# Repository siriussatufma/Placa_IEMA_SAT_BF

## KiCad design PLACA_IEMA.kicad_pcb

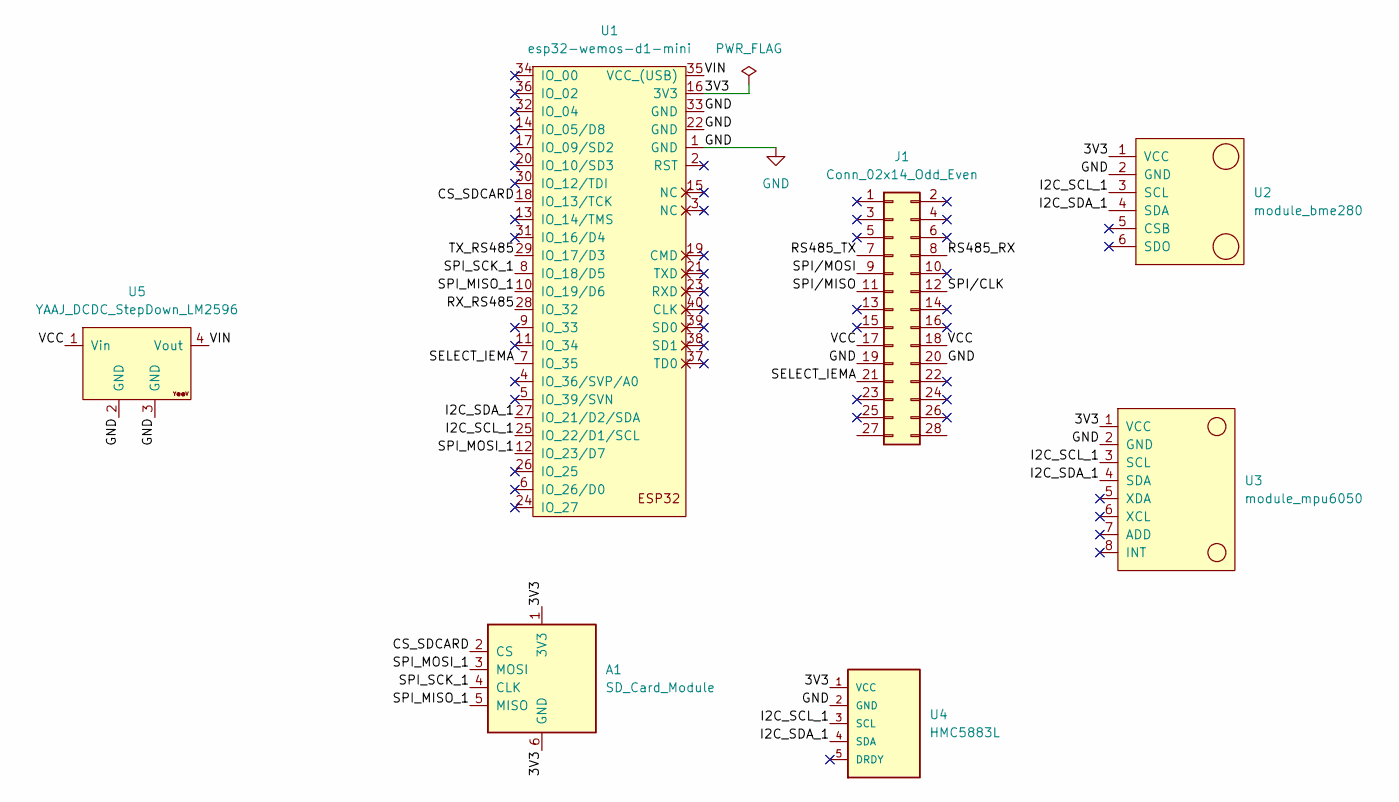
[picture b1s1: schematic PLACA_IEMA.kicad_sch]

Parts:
A1: SD_Card_Module
J1: Conn_02x14_Odd_Even; PinHeader_2x14_P2.54mm_Vertical
U1: esp32-wemos-d1-mini
U2: module_bme280
U3: module_mpu6050
U4: HMC5883L
U5: YAAJ_DCDC_StepDown_LM2596

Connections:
/3V3: A1.1 (3V3), A1.6 (GND), U1.16 (3V3), U2.1 (VCC), U3.1 (VCC), U4.1 (VCC)
/CS_SDCARD: A1.2 (CS), U1.18 (IO_13/TCK)
/GND: J1.19, J1.20, U1.1 (GND), U1.22 (GND), U1.33 (GND), U2.2 (GND), U3.2 (GND), U4.2 (GND), U5.2 (GND), U5.3 (GND)
/I2C_SCL_1: U1.25 (IO_22/D1/SCL), U2.3 (SCL), U3.3 (SCL), U4.3 (SCL)
/I2C_SDA_1: U1.27 (IO_21/D2/SDA), U2.4 (SDA), U3.4 (SDA), U4.4 (SDA)
/RS485_RX: J1.8
/RS485_TX: J1.7
/RX_RS485: U1.28 (IO_32)
/SELECT_IEMA: J1.21, U1.7 (IO_35)
/SPI_MISO_1: A1.5 (MISO), U1.10 (IO_19/D6)
/SPI_MOSI_1: A1.3 (MOSI), U1.12 (IO_23/D7)
/SPI_SCK_1: A1.4 (CLK), U1.8 (IO_18/D5)
/SPI/CLK: J1.12
/SPI/MISO: J1.11
/SPI/MOSI: J1.9
/TX_RS485: U1.29 (IO_17/D3)
/VCC: J1.17, J1.18, U5.1 (Vin)
/VIN: U1.35 (VCC_(USB)), U5.4 (Vout)

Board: 2 copper layers, 7 parts (2 on the bottom side), 11 nets, no tracks yet.
